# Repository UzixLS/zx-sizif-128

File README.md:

## Sizif-128

Easy-to-build minimalistic ZX Spectrum clone.

[(some random photos)](https://cloud.err200.net/index.php/s/73TR85tYZkMm8Ax?path=%2Fsizif-128)

Specifications:
- CPLD EPM7128SLC84 (128 macrocells)
- Z80 3.5 MHz
- 128K RAM
- AY-3-8910 (YM2149) mono sound
- Pentagon timings
- PAL encoder in CPLD (CRT TVs preferred)
- Intended to build on 9x15 prototyping board, but may be built on manufactured PCB

To modify and compile CPLD firmware you need Quartus 13.0sp1.
To modify schematic and pcb you need Kicad 6 or newer.

### Changelog
* Rev.A - first release. Please note the [errata](pcb/rev.A/ERRATA.txt).
* Rev.B - experimental PCB
    * 74HCU04-based tape input
    * added power LED
    * added reset button
    * removed NMI button
    * C20 replaced by variable variant to tune PAL color signal
* Rev.C
    * 74HCU04-based tape input reverted back to transistor-based
    * unused U6 inputs has been grounded
    * video circuit has been tuned for best colors
    * all pcb tracks are fancy now ;)
* Rev.C1
    * improve tape input sensitivity (thanks to SerOne from zx-pk forum)

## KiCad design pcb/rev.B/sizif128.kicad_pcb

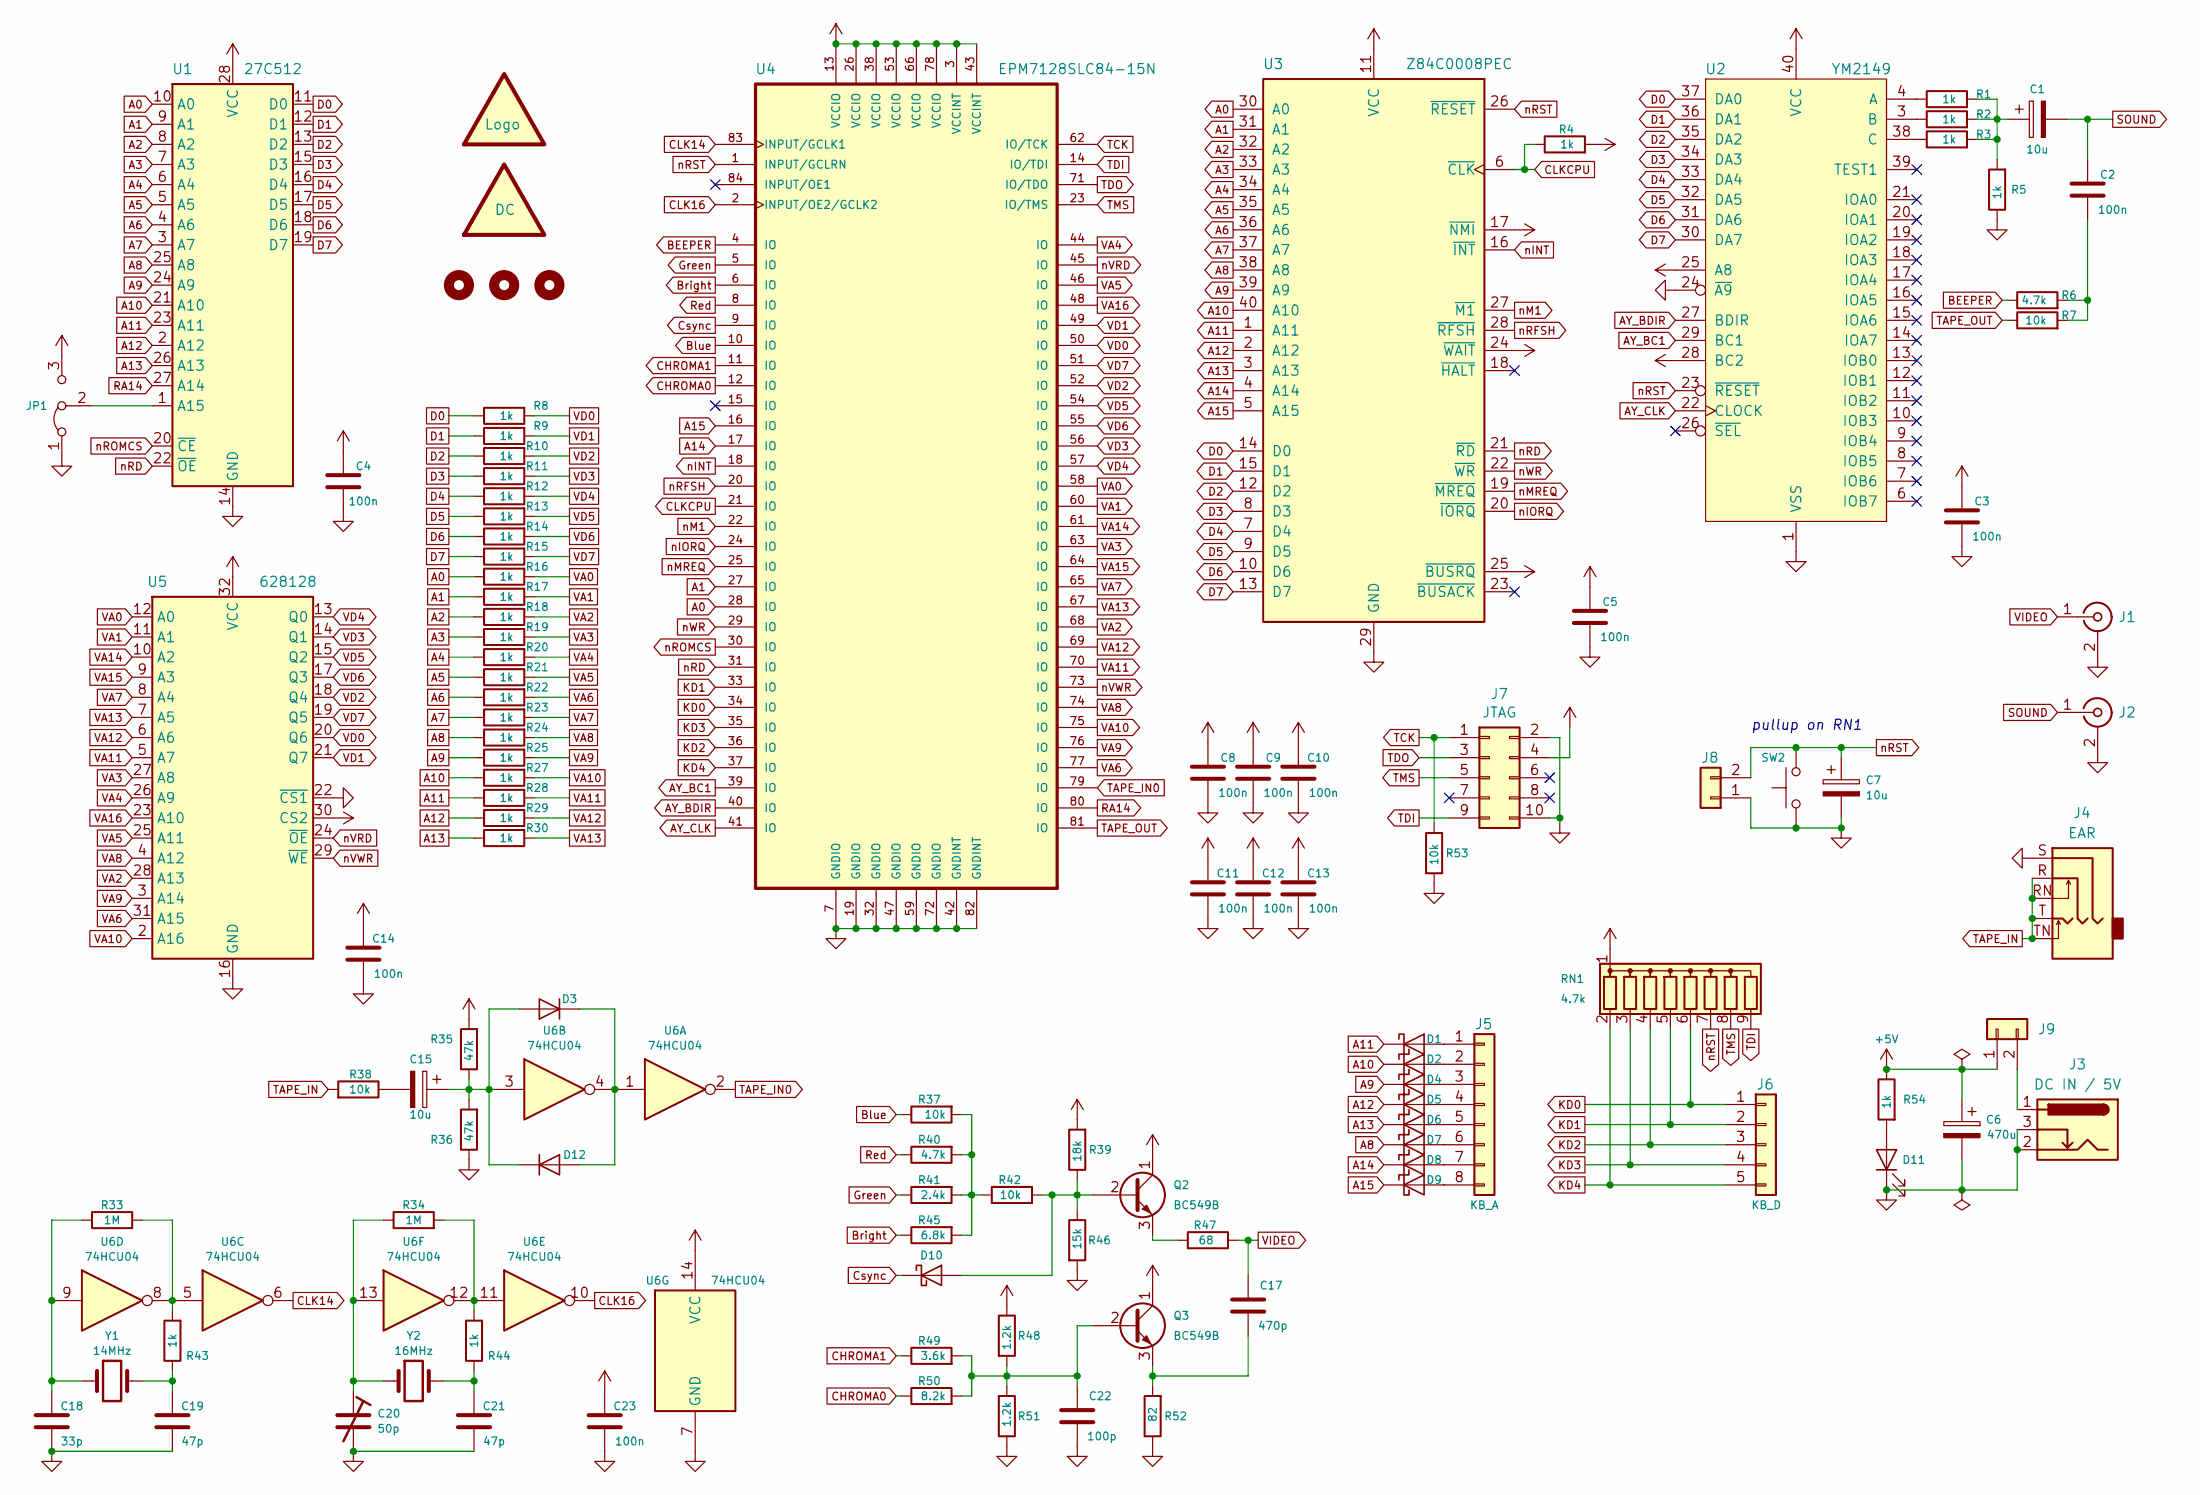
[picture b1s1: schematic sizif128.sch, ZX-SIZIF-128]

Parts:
C1, C7, C15: 10u; CP_Radial_D5.0mm_P2.00mm
C2, C3, C4, C5, C8, C9, C10, C11, C12, C13, C14, C23: 100n; C_Disc_D7.0mm_W2.5mm_P5.00mm
C6: 470u; CP_Radial_D10.0mm_P3.80mm
C17: 470p; C_Disc_D3.8mm_W2.6mm_P2.50mm
C18: 33p; C_Disc_D3.8mm_W2.6mm_P2.50mm
C19, C21: 47p; C_Disc_D3.8mm_W2.6mm_P2.50mm
C20: 50p; C_Trim_D6.3mm_P5.50mm
C22: 100p; C_Disc_D3.8mm_W2.6mm_P2.50mm
D1, D2, D4, D5, D6, D7, D8, D9, D10: BAT85; D_DO-35_SOD27_P7.62mm_Horizontal
D3, D12: 1N4148; D_DO-35_SOD27_P7.62mm_Horizontal
D11: LED; LED_D4.0mm
H1, H2, H3: MountingHole; MountingHole_3mm
J1, J2: RCJ-013; CUI_RCJ-013
J3: DS-210; BarrelJack_Horizontal
J4: PJ307; SWITCHCRAFT_35RAPC4BHN2
J5: Conn_01x08; PinSocket_1x08_P2.54mm_Vertical
J6: Conn_01x05; PinSocket_1x05_P2.54mm_Vertical
J7: Conn_02x05; PinHeader_2x05_P2.54mm_Vertical
J8, J9: Conn_01x02; PinHeader_1x02_P2.54mm_Vertical
JP1: Jumper_3_Bridged12; PinHeader_1x03_P2.54mm_Vertical
LOGO1: logo; black-mage2
LOGO2: logo; dc_center_positive_big
Q2, Q3: BC549B; TO-92_Inline
R1, R2, R3, R4, R5, R8, R9, R10, R11, R12, R13, R14, R15, R16, R17, R18, R19, R20, R21, R22, R23, R24, R25, R27, R28, R29, R30, R43, R44, R54: 1k; R_Axial_DIN0204_L3.6mm_D1.6mm_P7.62mm_Horizontal
R6, R40: 4.7k; R_Axial_DIN0204_L3.6mm_D1.6mm_P7.62mm_Horizontal
R7, R37, R38, R42, R53: 10k; R_Axial_DIN0204_L3.6mm_D1.6mm_P7.62mm_Horizontal
R33, R34: 1M; R_Axial_DIN0204_L3.6mm_D1.6mm_P7.62mm_Horizontal
R35, R36: 47k; R_Axial_DIN0204_L3.6mm_D1.6mm_P7.62mm_Horizontal
R39: 18k; R_Axial_DIN0204_L3.6mm_D1.6mm_P7.62mm_Horizontal
R41: 2.4k; R_Axial_DIN0204_L3.6mm_D1.6mm_P7.62mm_Horizontal
R45: 6.8k; R_Axial_DIN0204_L3.6mm_D1.6mm_P7.62mm_Horizontal
R46: 15k; R_Axial_DIN0204_L3.6mm_D1.6mm_P7.62mm_Horizontal
R47: 68; R_Axial_DIN0204_L3.6mm_D1.6mm_P7.62mm_Horizontal
R48, R51: 1.2k; R_Axial_DIN0204_L3.6mm_D1.6mm_P7.62mm_Horizontal
R49: 3.6k; R_Axial_DIN0204_L3.6mm_D1.6mm_P7.62mm_Horizontal
R50: 8.2k; R_Axial_DIN0204_L3.6mm_D1.6mm_P7.62mm_Horizontal
R52: 82; R_Axial_DIN0204_L3.6mm_D1.6mm_P7.62mm_Horizontal
RN1: 4.7k; R_Array_SIP9
SW2: SW_Push; SW_Tactile_SPST_Angled_PTS645Vx83-2LFS
U1: 27C512; DIP-28_W15.24mm_Socket
U2: YM2149; DIP-40_W15.24mm_Socket
U3: Z84C0008PEC; DIP-40_W15.24mm_Socket
U4: EPM7128SLC84-15N; PLCC-84_THT-Socket
U5: 628128; DIP-32_W15.24mm_Socket
U6: 74HCU04; DIP-14_W7.62mm_Socket
Y1: 14MHz; Crystal_HC49-U_Vertical
Y2: 16MHz; Crystal_HC49-U_Vertical

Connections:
+5V: C3.2, C4.2, C5.2, C6.1, C8.2, C9.2, C10.2, C11.2, C12.2, C13.2, C14.2, C23.2, J7.4, J9.1, JP1.3 (B), Q2.1 (C), Q3.1 (C), R4.2, R35.2, R39.2, R48.1, R54.1, RN1.1 (common), U1.28 (VCC), U2.25 (A8), U2.28 (BC2), U2.40 (VCC), U3.11 (VCC), U3.17 (~NMI~), U3.24 (~WAIT~), U3.25 (~BUSRQ~), U4.3 (VCCINT), U4.13 (VCCIO), U4.26 (VCCIO), U4.38 (VCCIO), U4.43 (VCCINT), U4.53 (VCCIO), U4.66 (VCCIO), U4.78 (VCCIO), U5.30 (CS2), U5.32 (VCC), U6.14 (VCC)
A0: R16.1, U1.10 (A0), U3.30 (A0), U4.28 (IO)
A1: R17.1, U1.9 (A1), U3.31 (A1), U4.27 (IO)
A2: R18.1, U1.8 (A2), U3.32 (A2)
A3: R19.1, U1.7 (A3), U3.33 (A3)
A4: R20.1, U1.6 (A4), U3.34 (A4)
A5: R21.1, U1.5 (A5), U3.35 (A5)
A6: R22.1, U1.4 (A6), U3.36 (A6)
A7: R23.1, U1.3 (A7), U3.37 (A7)
A8: D7.1 (K), R24.1, U1.25 (A8), U3.38 (A8)
A9: D4.1 (K), R25.1, U1.24 (A9), U3.39 (A9)
A10: D2.1 (K), R27.1, U1.21 (A10), U3.40 (A10)
A11: D1.1 (K), R28.1, U1.23 (A11), U3.1 (A11)
A12: D5.1 (K), R29.1, U1.2 (A12), U3.2 (A12)
A13: D6.1 (K), R30.1, U1.26 (A13), U3.3 (A13)
A14: D8.1 (K), U3.4 (A14), U4.17 (IO)
A15: D9.1 (K), U3.5 (A15), U4.16 (IO)
AY_BC1: U2.29 (BC1), U4.39 (IO)
AY_BDIR: U2.27 (BDIR), U4.40 (IO)
AY_CLK: U2.22 (CLOCK), U4.41 (IO)
BEEPER: R6.1, U4.4 (IO)
Blue: R37.1, U4.10 (IO)
Bright: R45.1, U4.6 (IO)
CHROMA0: R50.1, U4.12 (IO)
CHROMA1: R49.1, U4.11 (IO)
CLK14: U4.83 (INPUT/GCLK1), U6.6
CLK16: U4.2 (INPUT/OE2/GCLK2), U6.10
CLKCPU: R4.1, U3.6 (~CLK~), U4.21 (IO)
Csync: D10.1 (K), U4.9 (IO)
D0: R8.1, U1.11 (D0), U2.37 (DA0), U3.14 (D0)
D1: R9.1, U1.12 (D1), U2.36 (DA1), U3.15 (D1)
D2: R10.1, U1.13 (D2), U2.35 (DA2), U3.12 (D2)
D3: R11.1, U1.15 (D3), U2.34 (DA3), U3.8 (D3)
D4: R12.1, U1.16 (D4), U2.33 (DA4), U3.7 (D4)
D5: R13.1, U1.17 (D5), U2.32 (DA5), U3.9 (D5)
D6: R14.1, U1.18 (D6), U2.31 (DA6), U3.10 (D6)
D7: R15.1, U1.19 (D7), U2.30 (DA7), U3.13 (D7)
GND: C3.1, C4.1, C5.1, C6.2, C7.2, C8.1, C9.1, C10.1, C11.1, C12.1, C13.1, C14.1, C18.1, C19.1, C20.2, C21.1, C22.2, C23.1, D11.1 (K), J1.2 (Ext), J2.2 (Ext), J3.2, J3.3, J4.S, J7.2, J7.10, J8.1, JP1.1 (A), R5.1, R36.1, R46.2, R51.1, R52.1, R53.1, SW2.1, U1.14 (GND), U2.1 (VSS), U2.24 (~A9~), U3.29 (GND), U4.7 (GNDIO), U4.19 (GNDIO), U4.32 (GNDIO), U4.42 (GNDINT), U4.47 (GNDIO), U4.59 (GNDIO), U4.72 (GNDIO), U4.82 (GNDINT), U5.16 (GND), U5.22 (~CS1), U6.7 (GND)
Green: R41.1, U4.5 (IO)
KD0: J6.1, RN1.6 (R5), U4.34 (IO)
KD1: J6.2, RN1.5 (R4), U4.33 (IO)
KD2: J6.3, RN1.4 (R3), U4.36 (IO)
KD3: J6.4, RN1.3 (R2), U4.35 (IO)
KD4: J6.5, RN1.2 (R1), U4.37 (IO)
unnamed: C1.1, R1.2, R2.2, R3.2, R5.2
unnamed: C2.1, R6.2, R7.2
unnamed: C15.1, D3.2 (A), D12.1 (K), R35.1, R36.2, U6.3
unnamed: C15.2, R38.1
unnamed: C17.1, Q3.3 (E), R52.2
unnamed: C18.2, R33.1, U6.9, Y1.1
unnamed: C19.2, R43.1, Y1.2
unnamed: C20.1, R34.1, U6.13, Y2.1
unnamed: C21.2, R44.1, Y2.2
unnamed: C22.1, Q3.2 (B), R48.2, R49.2, R50.2, R51.2
unnamed: D1.2 (A), J5.1
unnamed: D2.2 (A), J5.2
unnamed: D4.2 (A), J5.3
unnamed: D5.2 (A), J5.4
unnamed: D6.2 (A), J5.5
unnamed: D7.2 (A), J5.6
unnamed: D8.2 (A), J5.7
unnamed: D9.2 (A), J5.8
unnamed: D10.2 (A), Q2.2 (B), R39.1, R42.2, R46.1
unnamed: D11.2 (A), R54.2
unnamed: D3.1 (K), D12.2 (A), U6.1, U6.4
unnamed: J3.1, J9.2
unnamed: JP1.2 (C), U1.1 (A15)
unnamed: Q2.3 (E), R47.2
unnamed: R1.1, U2.4 (A)
unnamed: R2.1, U2.3 (B)
unnamed: R3.1, U2.38 (C)
unnamed: R33.2, R43.2, U6.5, U6.8
unnamed: R34.2, R44.2, U6.11, U6.12
unnamed: R37.2, R40.2, R41.2, R42.1, R45.2
RA14: U1.27 (A14), U4.80 (IO)
Red: R40.1, U4.8 (IO)
SOUND: C1.2, C2.2, J2.1 (In)
TAPE_IN: J4.R, J4.RN, J4.T, J4.TN, R38.2
TAPE_IN0: U4.79 (IO), U6.2
TAPE_OUT: R7.1, U4.81 (IO)
TCK: J7.1, R53.2, U4.62 (IO/TCK)
TDI: J7.9, RN1.9 (R8), U4.14 (IO/TDI)
TDO: J7.3, U4.71 (IO/TDO)
TMS: J7.5, RN1.8 (R7), U4.23 (IO/TMS)
VA0: R16.2, U4.58 (IO), U5.12 (A0)
VA1: R17.2, U4.60 (IO), U5.11 (A1)
VA2: R18.2, U4.68 (IO), U5.28 (A13)
VA3: R19.2, U4.63 (IO), U5.27 (A8)
VA4: R20.2, U4.44 (IO), U5.26 (A9)
VA5: R21.2, U4.46 (IO), U5.25 (A11)
VA6: R22.2, U4.77 (IO), U5.31 (A15)
VA7: R23.2, U4.65 (IO), U5.8 (A4)
VA8: R24.2, U4.74 (IO), U5.4 (A12)
VA9: R25.2, U4.76 (IO), U5.3 (A14)
VA10: R27.2, U4.75 (IO), U5.2 (A16)
VA11: R28.2, U4.70 (IO), U5.5 (A7)
VA12: R29.2, U4.69 (IO), U5.6 (A6)
VA13: R30.2, U4.67 (IO), U5.7 (A5)
VA14: U4.61 (IO), U5.10 (A2)
VA15: U4.64 (IO), U5.9 (A3)
VA16: U4.48 (IO), U5.23 (A10)
VD0: R8.2, U4.50 (IO), U5.20 (Q6)
VD1: R9.2, U4.49 (IO), U5.21 (Q7)
VD2: R10.2, U4.52 (IO), U5.18 (Q4)
VD3: R11.2, U4.56 (IO), U5.14 (Q1)
VD4: R12.2, U4.57 (IO), U5.13 (Q0)
VD5: R13.2, U4.54 (IO), U5.15 (Q2)
VD6: R14.2, U4.55 (IO), U5.17 (Q3)
VD7: R15.2, U4.51 (IO), U5.19 (Q5)
VIDEO: C17.2, J1.1 (In), R47.1
nINT: U3.16 (~INT~), U4.18 (IO)
nIORQ: U3.20 (~IORQ~), U4.24 (IO)
nM1: U3.27 (~M1~), U4.22 (IO)
nMREQ: U3.19 (~MREQ~), U4.25 (IO)
nRD: U1.22 (~OE), U3.21 (~RD~), U4.31 (IO)
nRFSH: U3.28 (~RFSH~), U4.20 (IO)
nROMCS: U1.20 (~CE), U4.30 (IO)
nRST: C7.1, J8.2, RN1.7 (R6), SW2.2, U2.23 (~RESET~), U3.26 (~RESET~), U4.1 (INPUT/GCLRN)
nVRD: U4.45 (IO), U5.24 (~OE)
nVWR: U4.73 (IO), U5.29 (~WE)
nWR: U3.22 (~WR~), U4.29 (IO)

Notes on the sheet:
pullup on RN1

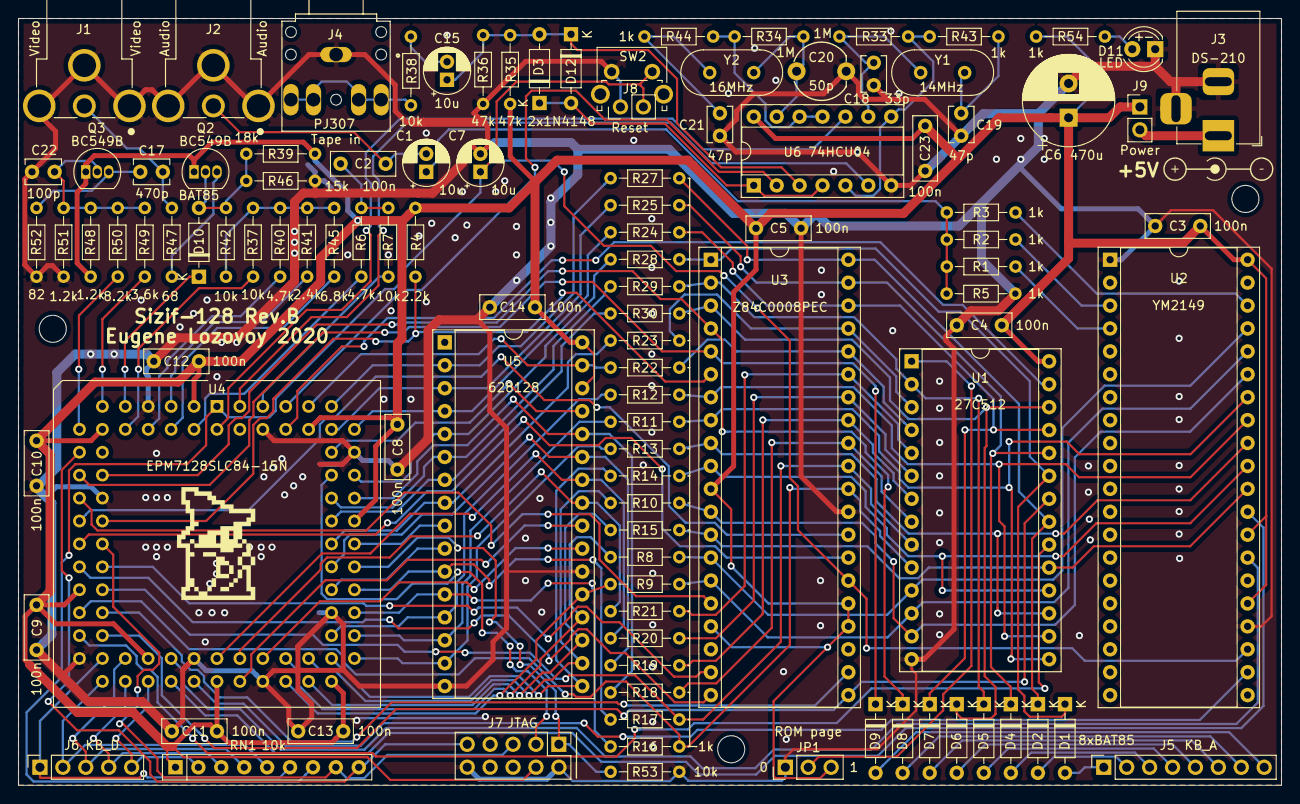
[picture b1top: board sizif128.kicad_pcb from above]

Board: 2 copper layers, 140.0 x 85.0 mm, 112 parts (0 on the bottom side), 121 nets.

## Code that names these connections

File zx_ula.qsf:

# -------------------------------------------------------------------------- #
#
# Copyright (C) 1991-2009 Altera Corporation
# Your use of Altera Corporation's design tools, logic functions 
# and other software and tools, and its AMPP partner logic 
# functions, and any output files from any of the foregoing 
# (including device programming or simulation files), and any 
# associated documentation or information are expressly subject 
# to the terms and conditions of the Altera Program License 
# Subscription Agreement, Altera MegaCore Function License 
# Agreement, or other applicable license agreement, including, 
# without limitation, that your use is for the sole purpose of 
# programming logic devices manufactured by Altera and sold by 
# Altera or its authorized distributors.  Please refer to the 
# applicable agreement for further details.
#
# -------------------------------------------------------------------------- #
#
# Quartus II
# Version 9.0 Build 235 06/17/2009 Service Pack 2 SJ Web Edition
# Date created = 08:15:12  April 28, 2019
#
# -------------------------------------------------------------------------- #
#
# Notes:
#
# 1) The default values for assignments are stored in the file:
#		zx_ula_assignment_defaults.qdf
#    If this file doesn't exist, see file:
#		assignment_defaults.qdf
#
# 2) Altera recommends that you do not modify this file. This
#    file is updated automatically by the Quartus II software
#    and any changes you make may be lost or overwritten.
#
# -------------------------------------------------------------------------- #


set_global_assignment -name FAMILY MAX7000S
set_global_assignment -name DEVICE "EPM7128SLC84-15"
set_global_assignment -name TOP_LEVEL_ENTITY zx_ula
set_global_assignment -name ORIGINAL_QUARTUS_VERSION "9.0 SP2"
set_global_assignment -name PROJECT_CREATION_TIME_DATE "08:15:12  APRIL 28, 2019"
set_global_assignment -name LAST_QUARTUS_VERSION "9.0 SP2"
set_global_assignment -name USE_GENERATED_PHYSICAL_CONSTRAINTS OFF -section_id eda_blast_fpga
set_global_assignment -name DEVICE_FILTER_SPEED_GRADE 15
set_global_assignment -name MIN_CORE_JUNCTION_TEMP 0
set_global_assignment -name MAX_CORE_JUNCTION_TEMP 85
set_global_assignment -name MAX7000_DEVICE_IO_STANDARD TTL
set_location_assignment PIN_10 -to b
set_location_assignment PIN_4 -to beeper
set_location_assignment PIN_83 -to clk14
set_location_assignment PIN_21 -to clkcpu
set_location_assignment PIN_5 -to g
set_location_assignment PIN_18 -to n_int
set_location_assignment PIN_24 -to n_iorq
set_location_assignment PIN_22 -to n_m1
set_location_assignment PIN_25 -to n_mreq
set_location_assignment PIN_31 -to n_rd
set_location_assignment PIN_20 -to n_rfsh
set_location_assignment PIN_30 -to n_romcs
set_location_assignment PIN_45 -to n_vrd
set_location_assignment PIN_73 -to n_vwr
set_location_assignment PIN_29 -to n_wr
set_location_assignment PIN_8 -to r
set_location_assignment PIN_1 -to rst_n
set_location_assignment PIN_81 -to tape_out
set_location_assignment PIN_48 -to va[16]
set_location_assignment PIN_64 -to va[15]
set_location_assignment PIN_61 -to va[14]
set_location_assignment PIN_67 -to va[13]
set_location_assignment PIN_69 -to va[12]
set_location_assignment PIN_70 -to va[11]
set_location_assignment PIN_75 -to va[10]
set_location_assignment PIN_76 -to va[9]
set_location_assignment PIN_74 -to va[8]
set_location_assignment PIN_65 -to va[7]
set_location_assignment PIN_77 -to va[6]
set_location_assignment PIN_46 -to va[5]
set_location_assignment PIN_44 -to va[4]
set_location_assignment PIN_63 -to va[3]
set_location_assignment PIN_68 -to va[2]
set_location_assignment PIN_60 -to va[1]
set_location_assignment PIN_58 -to va[0]
set_location_assignment PIN_51 -to vd[7]
set_location_assignment PIN_55 -to vd[6]
set_location_assignment PIN_54 -to vd[5]
set_location_assignment PIN_57 -to vd[4]
set_location_assignment PIN_56 -to vd[3]
set_location_assignment PIN_52 -to vd[2]
set_location_assignment PIN_49 -to vd[1]
set_location_assignment PIN_50 -to vd[0]
set_global_assignment -name VERILOG_INPUT_VERSION SYSTEMVERILOG_2005
set_global_assignment -name VERILOG_SHOW_LMF_MAPPING_MESSAGES OFF
set_global_assignment -name MAX7000_OPTIMIZATION_TECHNIQUE AREA
set_global_assignment -name FMAX_REQUIREMENT "14 MHz"
set_global_assignment -name FMAX_REQUIREMENT "14 MHz" -section_id clk14
set_location_assignment PIN_6 -to i
set_instance_assignment -name CLOCK_SETTINGS clk14 -to clk14
set_instance_assignment -name CLOCK_SETTINGS clkcpu -to clkcpu
set_location_assignment PIN_28 -to a0
set_location_assignment PIN_27 -to a1
set_location_assignment PIN_17 -to a14
set_location_assignment PIN_16 -to a15
set_global_assignment -name AUTO_RESOURCE_SHARING OFF
set_global_assignment -name AUTO_LCELL_INSERTION OFF
set_location_assignment PIN_9 -to csync
set_location_assignment PIN_2 -to clk16
set_location_assignment PIN_11 -to chroma[1]
set_location_assignment PIN_12 -to chroma[0]
set_location_assignment PIN_33 -to kd[1]
set_location_assignment PIN_34 -to kd[0]
set_location_assignment PIN_35 -to kd[3]
set_location_assignment PIN_36 -to kd[2]
set_location_assignment PIN_37 -to kd[4]
set_location_assignment PIN_39 -to ay_bc1
set_location_assignment PIN_40 -to ay_bdir
set_location_assignment PIN_41 -to ay_clk
set_location_assignment PIN_79 -to tape_in
set_location_assignment PIN_80 -to ra14
set_global_assignment -name FMAX_REQUIREMENT "16 MHz" -section_id clk16
set_instance_assignment -name CLOCK_SETTINGS clk16 -to clk16
set_global_assignment -name BASED_ON_CLOCK_SETTINGS clk14 -section_id clkcpu
set_global_assignment -name MULTIPLY_BASE_CLOCK_PERIOD_BY 2 -section_id clkcpu
set_global_assignment -name OPTIMIZE_HOLD_TIMING OFF
set_global_assignment -name FITTER_EFFORT "STANDARD FIT"
set_global_assignment -name AUTO_TURBO_BIT ON
set_global_assignment -name OPTIMIZE_IOC_REGISTER_PLACEMENT_FOR_TIMING ON
set_global_assignment -name SAVE_DISK_SPACE OFF
set_global_assignment -name FIT_ONLY_ONE_ATTEMPT OFF
set_global_assignment -name SLOW_SLEW_RATE OFF
set_global_assignment -name PROJECT_OUTPUT_DIRECTORY output/
set_global_assignment -name VHDL_FILE chroma_gen16.vhd
set_global_assignment -name VERILOG_FILE top.v
set_global_assignment -name VERILOG_INCLUDE_FILE util.vh

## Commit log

2020-02-16 initial
2020-02-16 working version
2020-04-19 some refactor. correct timings
2020-04-19 add license
2020-04-19 cleanup quartus project files
2020-04-19 reorganize repository
2020-04-19 add pcb
2020-04-19 add delivered files (gerbers, firmware binary, etc)
2020-04-19 add rom
2020-04-19 add readme
2020-05-17 fix github language detector
2020-08-15 add testbench
2020-08-15 update firmware
    1. quartus 13 may be used for build now;
    2. fix small border offset;
    3. fix too fast flashing with attribute bit 7.
2020-08-15 fix missing tape loading sound
2020-10-12 pcb: move old files to rev.A folder
2020-10-12 update cpld firmware
2020-10-12 clocks.sdc: slightly tune chroma clock just to be safe
2020-10-12 remove util.vh
2020-10-12 pcb rev.A: add errata
2020-10-12 rewrite chroma_gen in verilog
2020-10-12 git: fix CRLF
2020-10-12 cpld: tune video generation to improve quality
2020-10-26 cpld: do not stop screen render on reset
2020-10-29 pcb rev.A: add R49=3.6k to errata
2021-03-18 chroma_gen: handle new clock frequencies
    28.375 MHz (best result, recommended to use instead of 16 MHz)
    28.63636 MHz
    35.46895 MHz
2021-04-08 gitignore, gitattributes: add kicad 6 entries
2021-04-08 add photos
2021-04-25 chroma_gen: add comment how to calculate carrier
2021-04-25 fix #7ffd port decoding
    This commit improve compatibility with bunch of software like:
    - Eye Ache 2 by Code Busters
    - 70908 by Scoopex (trd version)
    - Void by Invaders (RU version)
2021-11-08 update gitignore
2022-06-19 update 3d view
2022-07-09 cpld: minor refactor
2022-07-09 cpld: refactor video color signal generation
    assume 28.375MHz Y2 by default
2022-07-10 convert png to webp
2022-07-10 add pcb rev.B
2022-07-10 add pcb rev.C1 gerbers, pdf, etc...
2022-07-10 add pcb rev.C1
2022-07-10 add pcb rev.C
2022-07-10 update cpld fimrware. add variants for 16MHz and 28.375MHz crystals
2022-08-20 add rev.C photo
2026-06-17 remove raw=true from README links
